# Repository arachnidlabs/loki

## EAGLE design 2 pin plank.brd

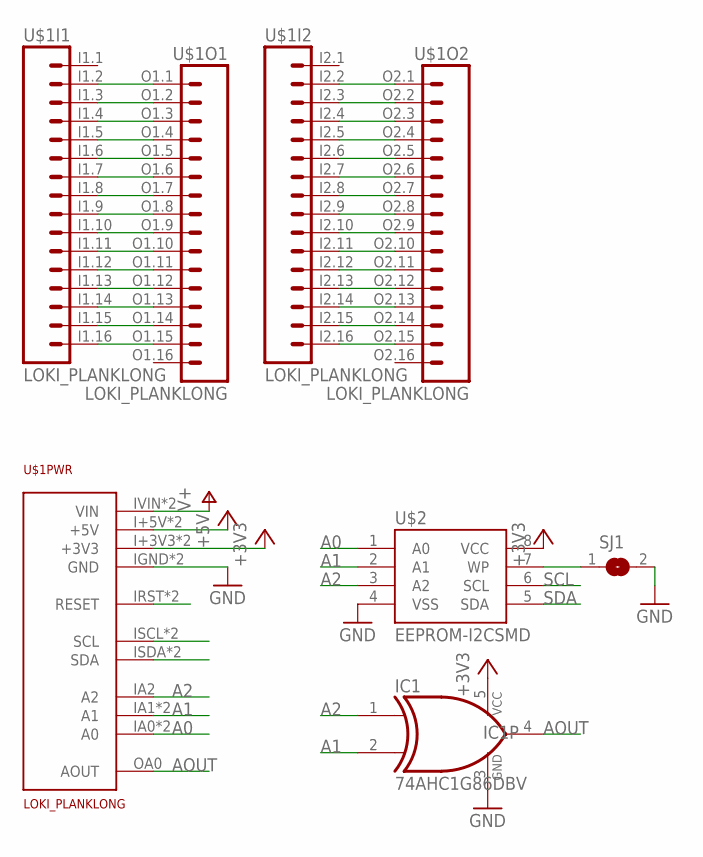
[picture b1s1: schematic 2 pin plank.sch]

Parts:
IC1: 74AHC1G86DBV; SOT23-5
SJ1: SJ
U$1: LOKI_PLANKLONG; PLANK_LONG
U$2: EEPROM-I2CSMD; SO08

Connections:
+3V3: IC1.5 (VCC), U$1.I+3V3 (+3V3), U$1.O+3V3 (+3V3), U$2.8 (VCC)
+5V: U$1.I+5V (+5V), U$1.O+5V (+5V)
A0: U$1.IA0 (A0), U$1.OA1 (A0), U$2.1 (A0)
A1: IC1.2 (I1), U$1.IA1 (A1), U$1.OA2 (A1), U$2.2 (A1)
A2: IC1.1 (I0), U$1.IA2 (A2), U$2.3 (A2)
AOUT: IC1.4 (O), U$1.OA0 (AOUT)
GND: IC1.3 (GND), SJ1.2, U$1.IGND (GND), U$1.OGND (GND), U$2.4 (VSS)
unnamed: U$1.I1.16 (16), U$1.O1.15 (15)
unnamed: U$1.I1.15 (15), U$1.O1.14 (14)
unnamed: U$1.I1.14 (14), U$1.O1.13 (13)
unnamed: U$1.I1.13 (13), U$1.O1.12 (12)
unnamed: U$1.I1.12 (12), U$1.O1.11 (11)
unnamed: U$1.I1.11 (11), U$1.O1.10 (10)
unnamed: U$1.I1.10 (10), U$1.O1.9 (9)
unnamed: U$1.I1.9 (9), U$1.O1.8 (8)
unnamed: U$1.I1.8 (8), U$1.O1.7 (7)
unnamed: U$1.I1.7 (7), U$1.O1.6 (6)
unnamed: U$1.I1.6 (6), U$1.O1.5 (5)
unnamed: U$1.I1.5 (5), U$1.O1.4 (4)
unnamed: U$1.I1.4 (4), U$1.O1.3 (3)
unnamed: U$1.I1.3 (3), U$1.O1.2 (2)
unnamed: U$1.I1.2 (2), U$1.O1.1 (1)
unnamed: U$1.I2.16 (16), U$1.O2.15 (15)
unnamed: U$1.I2.15 (15), U$1.O2.14 (14)
unnamed: U$1.I2.14 (14), U$1.O2.13 (13)
unnamed: U$1.I2.13 (13), U$1.O2.12 (12)
unnamed: U$1.I2.12 (12), U$1.O2.11 (11)
unnamed: U$1.I2.11 (11), U$1.O2.10 (10)
unnamed: U$1.I2.10 (10), U$1.O2.9 (9)
unnamed: U$1.I2.9 (9), U$1.O2.8 (8)
unnamed: U$1.I2.8 (8), U$1.O2.7 (7)
unnamed: U$1.I2.7 (7), U$1.O2.6 (6)
unnamed: U$1.I2.6 (6), U$1.O2.5 (5)
unnamed: U$1.I2.5 (5), U$1.O2.4 (4)
unnamed: U$1.I2.4 (4), U$1.O2.3 (3)
unnamed: U$1.I2.3 (3), U$1.O2.2 (2)
unnamed: U$1.I2.2 (2), U$1.O2.1 (1)
unnamed: SJ1.1, U$2.7 (WP)
unnamed: U$1.IRST (RESET), U$1.ORST (RESET)
SCL: U$1.ISCL (SCL), U$1.OSCL (SCL), U$2.6 (SCL)
SDA: U$1.ISDA (SDA), U$1.OSDA (SDA), U$2.5 (SDA)
V+: U$1.IVIN (VIN), U$1.OVIN (VIN)

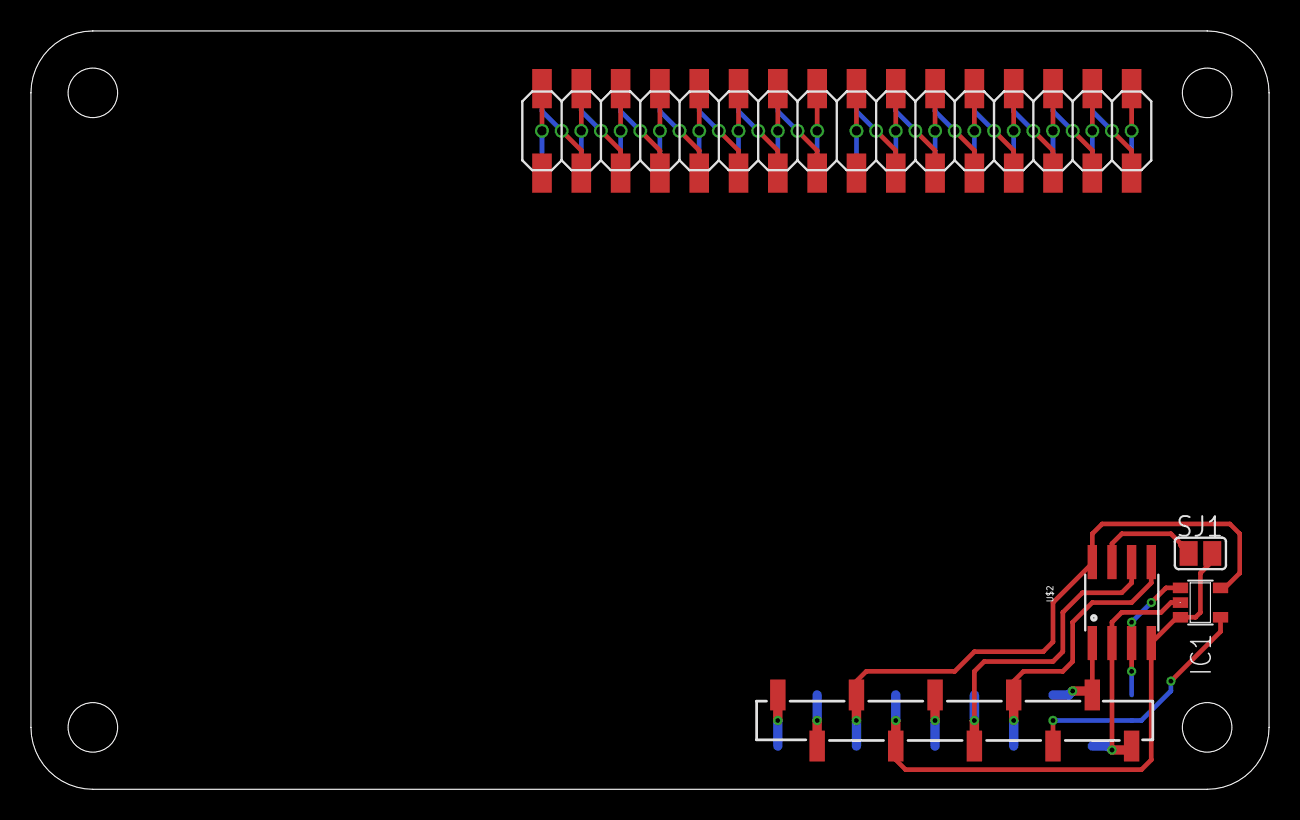
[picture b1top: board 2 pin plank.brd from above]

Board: 2 copper layers, 80.0 x 49.0 mm, 4 parts (0 on the bottom side), 42 nets.

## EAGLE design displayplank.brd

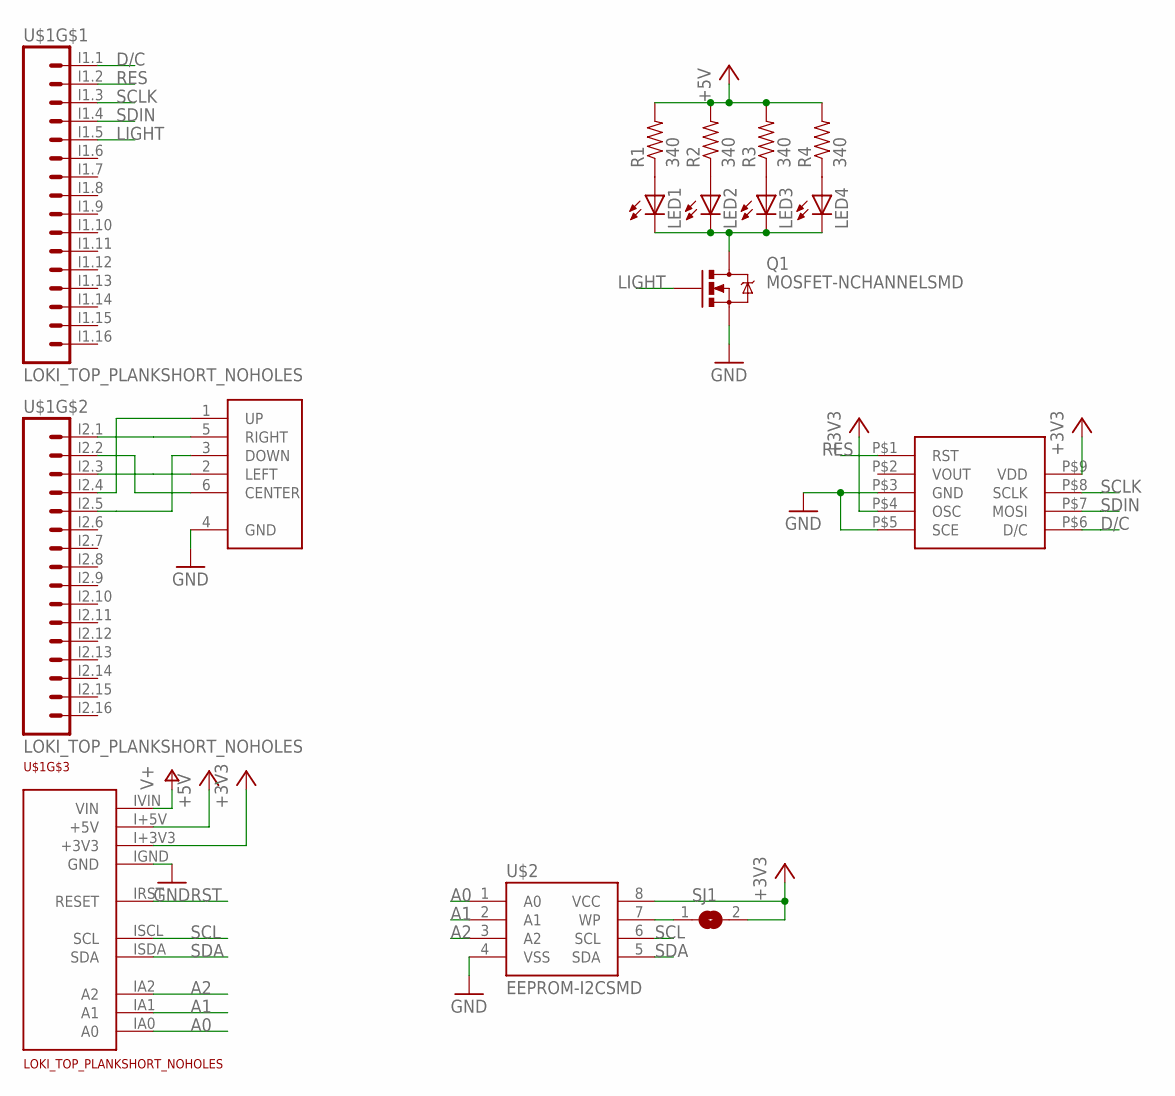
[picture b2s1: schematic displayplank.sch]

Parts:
LED1, LED2, LED3, LED4: LEDSML0805; SML0805
Q1: MOSFET-NCHANNELSMD; SOT23-3
R1, R2, R3, R4: 340; 0603-RES
SJ1: SJ
U$1: LOKI_TOP_PLANKSHORT_NOHOLES; TOP_PLANK_SHORT_NOHOLES
U$2: EEPROM-I2CSMD; SO08
U$3: JOYSTICK-10MM
U$5: 5110-SCREEN

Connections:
+3V3: SJ1.2, U$1.I+3V3 (+3V3), U$2.8 (VCC), U$5.P$4 (OSC), U$5.P$9 (VDD)
+5V: R1.2, R2.2, R3.2, R4.2, U$1.I+5V (+5V)
A0: U$1.IA0 (A0), U$2.1 (A0)
A1: U$1.IA1 (A1), U$2.2 (A1)
A2: U$1.IA2 (A2), U$2.3 (A2)
D/C: U$1.I1.1 (1), U$5.P$6 (D/C)
GND: Q1.2 (S), U$1.IGND (GND), U$2.4 (VSS), U$3.4 (GND), U$5.P$3 (GND), U$5.P$5 (SCE)
LIGHT: Q1.1 (G), U$1.I1.5 (5)
unnamed: SJ1.1, U$2.7 (WP)
unnamed: LED1.A, R1.1
unnamed: LED2.A, R2.1
unnamed: LED3.A, R3.1
unnamed: LED4.A, R4.1
unnamed: LED1.C, LED2.C, LED3.C, LED4.C, Q1.3 (D)
unnamed: U$1.I2.4 (4), U$3.1 (UP)
unnamed: U$1.I2.2 (2), U$3.6 (CENTER)
unnamed: U$1.I2.3 (3), U$3.2 (LEFT)
unnamed: U$1.I2.5 (5), U$3.3 (DOWN)
unnamed: U$1.I2.1 (1), U$3.5 (RIGHT)
RES: U$1.I1.2 (2), U$5.P$1 (RST)
RST: U$1.IRST (RESET)
SCL: U$1.ISCL (SCL), U$2.6 (SCL)
SCLK: U$1.I1.3 (3), U$5.P$8 (SCLK)
SDA: U$1.ISDA (SDA), U$2.5 (SDA)
SDIN: U$1.I1.4 (4), U$5.P$7 (MOSI)
V+: U$1.IVIN (VIN)

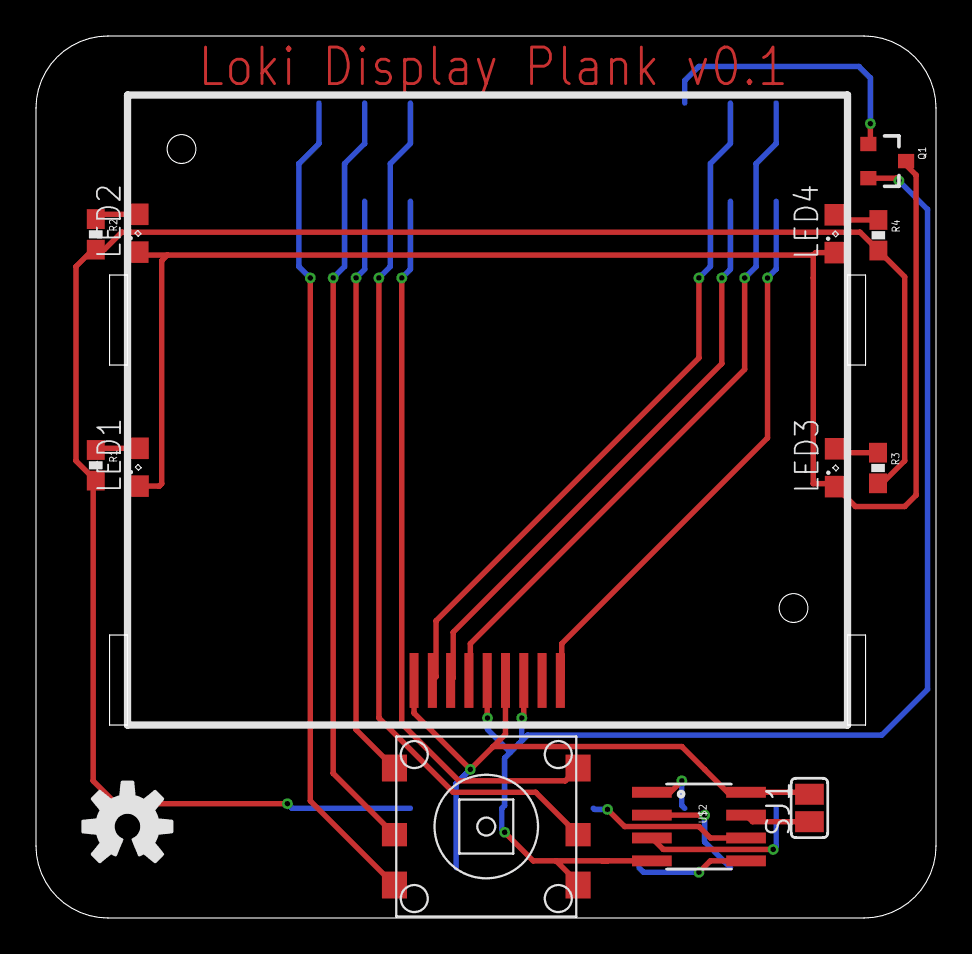
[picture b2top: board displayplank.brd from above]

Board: 2 copper layers, 50.0 x 49.0 mm, 15 parts (0 on the bottom side), 24 nets.

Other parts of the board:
U$4: OSHW-LOGO-M

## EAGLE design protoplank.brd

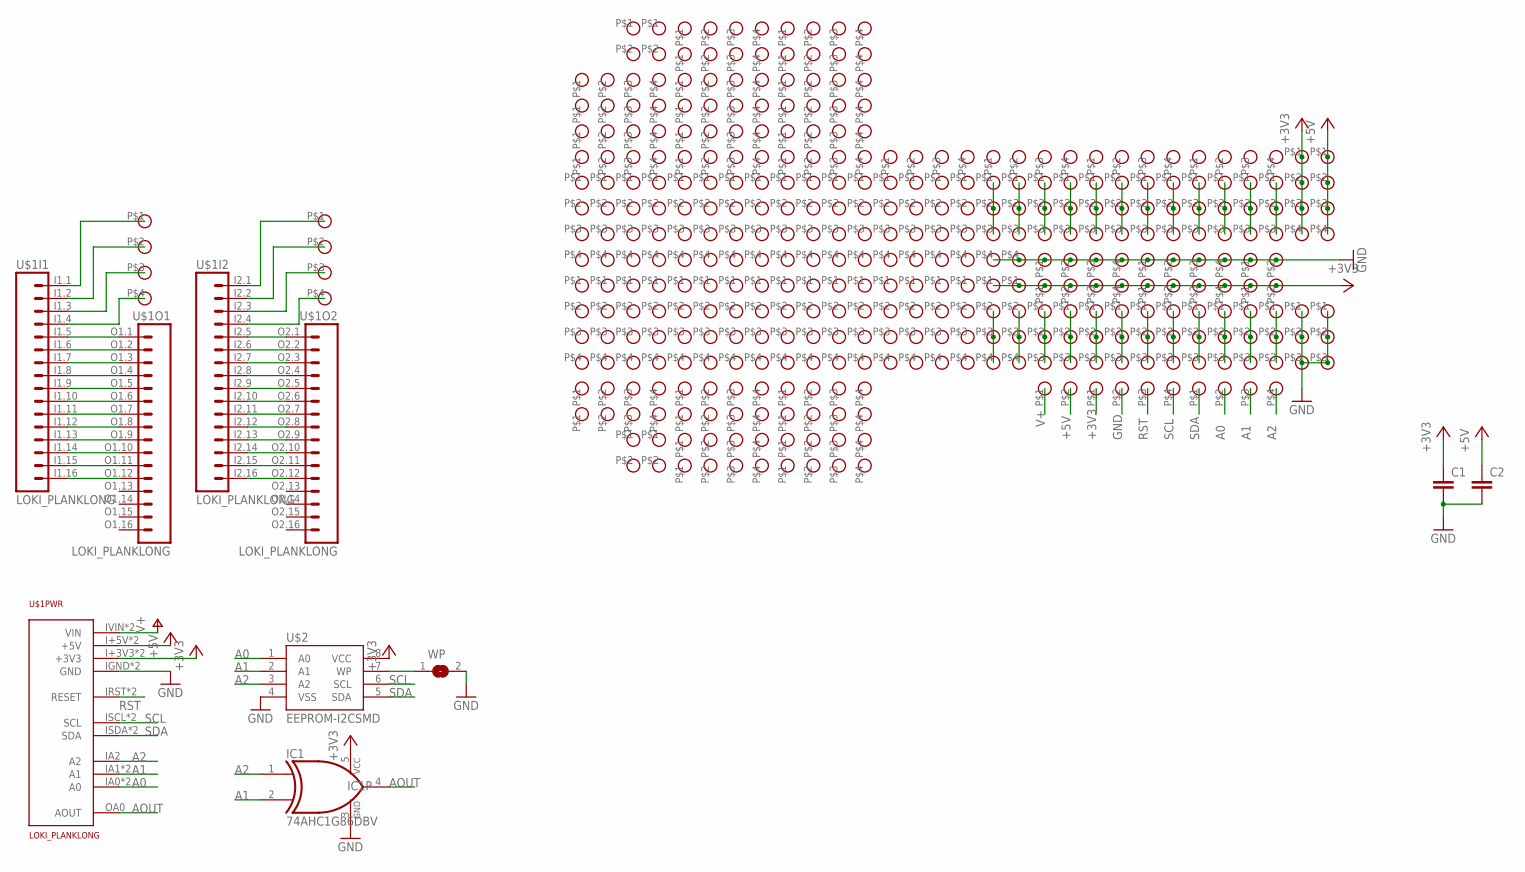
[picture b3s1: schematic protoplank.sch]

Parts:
C1, C2: CAPPTH; CAP-PTH-SMALL
IC1: 74AHC1G86DBV; SOT23-5
U$1: LOKI_PLANKLONG; PLANK_LONG
U$2: EEPROM-I2CSMD; SO08
U$3, U$4, U$5, U$6, U$7, U$8, U$9, U$10, U$11, U$12, U$13, U$14, U$15, U$16, U$17, U$18, U$19, U$20, U$21, U$22, U$78, U$80: PROTOPAD-3
U$23, U$24, U$25, U$26, U$34, U$35, U$36, U$37, U$38, U$39, U$40, U$41, U$42, U$43, U$44, U$45, U$46, U$47, U$48, U$49, U$50, U$51, U$52, U$53, U$54, U$55, U$56, U$57, U$58, U$59, U$60, U$61, U$62, U$63, U$64, U$65, U$66, U$67, U$68, U$69, U$70, U$71, U$72, U$73, U$74, U$75, U$76, U$77, U$79, U$81, U$82, U$83, U$84, U$85, U$86, U$87, U$88, U$89, U$90, U$91, U$92, U$93, U$94, U$95, U$96, U$97, U$98, U$99, U$100, U$101, U$102, U$103: PROTOPAD-4SQUARE; PROTOPAD-4
U$27, U$28, U$104, U$105, U$106, U$107: PROTOPAD-2SQUARE; PROTOPAD-2
U$29, U$30, U$31, U$32: PROTOPAD-4ROUND; PROTOPAD-4-ROUND
U$33: PROTOPAD-2ROUND; PROTOPAD-2-ROUND
WP: SJ

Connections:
+3V3: C1.1, IC1.5 (VCC), U$1.I+3V3 (+3V3), U$1.O+3V3 (+3V3), U$2.8 (VCC), U$25.P$1, U$25.P$2, U$25.P$3, U$25.P$4, U$26.P$1, U$26.P$2, U$26.P$3, U$26.P$4, U$28.P$1, U$28.P$2, U$32.P$1, U$35.P$1, U$36.P$1, U$77.P$1, U$77.P$2, U$77.P$3, U$77.P$4
+5V: C2.1, U$1.I+5V (+5V), U$1.O+5V (+5V), U$33.P$2, U$79.P$1, U$79.P$2, U$79.P$3, U$79.P$4
A0: U$1.IA0 (A0), U$1.OA1 (A0), U$2.1 (A0), U$31.P$2
A1: IC1.2 (I1), U$1.IA1 (A1), U$1.OA2 (A1), U$2.2 (A1), U$31.P$3
A2: IC1.1 (I0), U$1.IA2 (A2), U$2.3 (A2), U$31.P$4
AOUT: IC1.4 (O), U$1.OA0 (AOUT)
GND: C1.2, C2.2, IC1.3 (GND), U$1.IGND (GND), U$1.OGND (GND), U$2.4 (VSS), U$23.P$1, U$23.P$2, U$23.P$3, U$23.P$4, U$24.P$1, U$24.P$2, U$24.P$3, U$24.P$4, U$27.P$1, U$27.P$2, U$32.P$2, U$34.P$4, U$37.P$4, U$78.P$1, U$78.P$2, U$78.P$3, U$80.P$1, U$80.P$2, U$80.P$3, WP.2
unnamed: U$1.I1.16 (16), U$1.O1.12 (12)
unnamed: U$1.I1.15 (15), U$1.O1.11 (11)
unnamed: U$1.I1.14 (14), U$1.O1.10 (10)
unnamed: U$1.I1.13 (13), U$1.O1.9 (9)
unnamed: U$1.I1.12 (12), U$1.O1.8 (8)
unnamed: U$1.I1.11 (11), U$1.O1.7 (7)
unnamed: U$1.I1.10 (10), U$1.O1.6 (6)
unnamed: U$1.I1.9 (9), U$1.O1.5 (5)
unnamed: U$1.I1.8 (8), U$1.O1.4 (4)
unnamed: U$1.I1.7 (7), U$1.O1.3 (3)
unnamed: U$1.I1.6 (6), U$1.O1.2 (2)
unnamed: U$1.I1.5 (5), U$1.O1.1 (1)
unnamed: U$1.I2.16 (16), U$1.O2.12 (12)
unnamed: U$1.I2.15 (15), U$1.O2.11 (11)
unnamed: U$1.I2.14 (14), U$1.O2.10 (10)
unnamed: U$1.I2.13 (13), U$1.O2.9 (9)
unnamed: U$1.I2.12 (12), U$1.O2.8 (8)
unnamed: U$1.I2.11 (11), U$1.O2.7 (7)
unnamed: U$1.I2.10 (10), U$1.O2.6 (6)
unnamed: U$1.I2.9 (9), U$1.O2.5 (5)
unnamed: U$1.I2.8 (8), U$1.O2.4 (4)
unnamed: U$1.I2.7 (7), U$1.O2.3 (3)
unnamed: U$1.I2.6 (6), U$1.O2.2 (2)
unnamed: U$1.I2.5 (5), U$1.O2.1 (1)
unnamed: U$1.I1.4 (4), U$29.P$4
unnamed: U$1.I1.3 (3), U$29.P$3
unnamed: U$1.I1.2 (2), U$29.P$2
unnamed: U$1.I1.1 (1), U$29.P$1
unnamed: U$1.I2.4 (4), U$30.P$4
unnamed: U$1.I2.3 (3), U$30.P$3
unnamed: U$2.7 (WP), WP.1
unnamed: U$3.P$1, U$3.P$2, U$3.P$3
unnamed: U$1.I2.2 (2), U$30.P$2
unnamed: U$1.I2.1 (1), U$30.P$1
unnamed: U$4.P$1, U$4.P$2, U$4.P$3
unnamed: U$5.P$1, U$5.P$2, U$5.P$3
unnamed: U$6.P$1, U$6.P$2, U$6.P$3
unnamed: U$7.P$1, U$7.P$2, U$7.P$3
unnamed: U$8.P$1, U$8.P$2, U$8.P$3
unnamed: U$9.P$1, U$9.P$2, U$9.P$3
unnamed: U$10.P$1, U$10.P$2, U$10.P$3
unnamed: U$11.P$1, U$11.P$2, U$11.P$3
unnamed: U$12.P$1, U$12.P$2, U$12.P$3
unnamed: U$13.P$1, U$13.P$2, U$13.P$3
unnamed: U$14.P$1, U$14.P$2, U$14.P$3
unnamed: U$15.P$1, U$15.P$2, U$15.P$3
unnamed: U$16.P$1, U$16.P$2, U$16.P$3
unnamed: U$17.P$1, U$17.P$2, U$17.P$3
unnamed: U$18.P$1, U$18.P$2, U$18.P$3
unnamed: U$19.P$1, U$19.P$2, U$19.P$3
unnamed: U$20.P$1, U$20.P$2, U$20.P$3
unnamed: U$21.P$1, U$21.P$2, U$21.P$3
unnamed: U$22.P$1, U$22.P$2, U$22.P$3
unnamed: U$34.P$1, U$34.P$2, U$34.P$3
unnamed: U$37.P$1, U$37.P$2, U$37.P$3
unnamed: U$35.P$2, U$35.P$3, U$35.P$4
unnamed: U$36.P$2, U$36.P$3, U$36.P$4
RST: U$1.IRST (RESET), U$1.ORST (RESET), U$32.P$3
SCL: U$1.ISCL (SCL), U$1.OSCL (SCL), U$2.6 (SCL), U$32.P$4
SDA: U$1.ISDA (SDA), U$1.OSDA (SDA), U$2.5 (SDA), U$31.P$1
V+: U$1.IVIN (VIN), U$1.OVIN (VIN), U$33.P$1

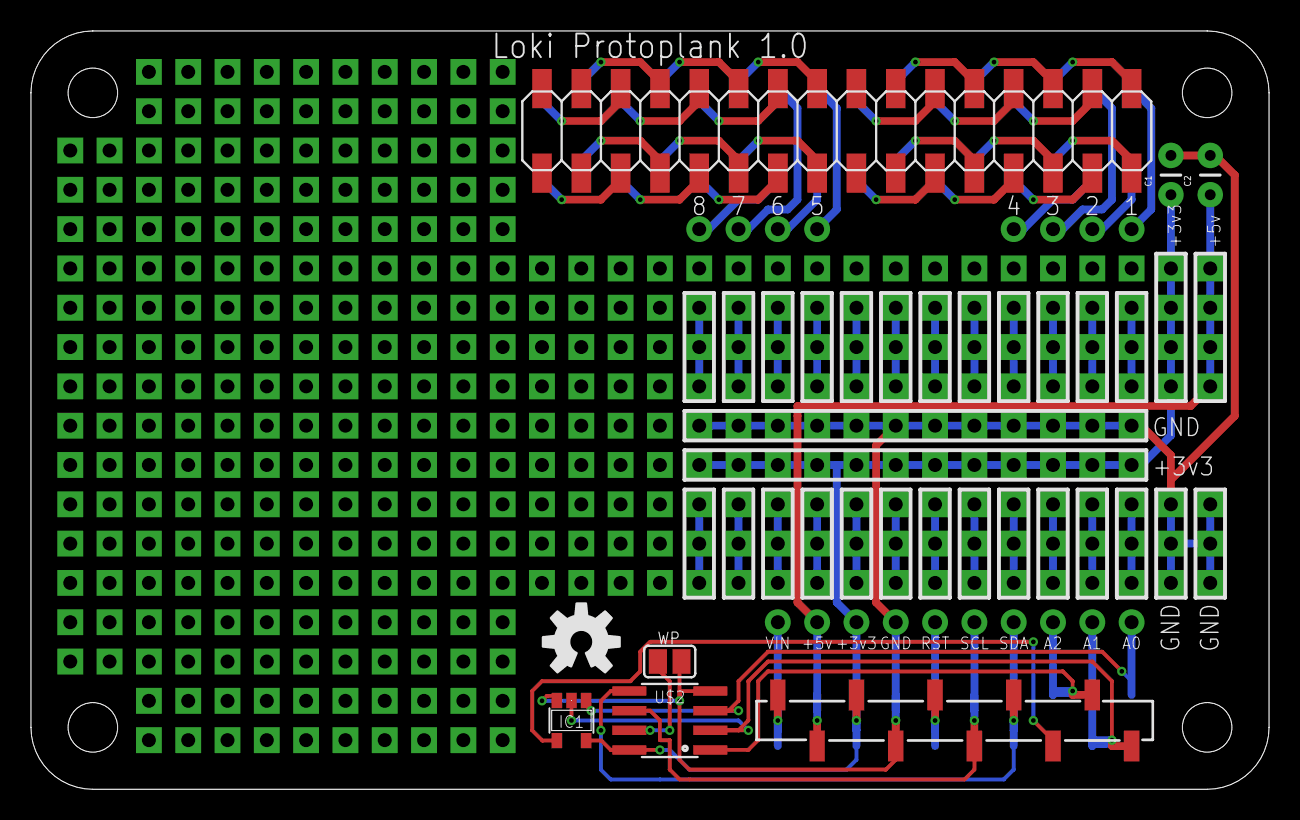
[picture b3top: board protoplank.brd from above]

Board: 2 copper layers, 80.0 x 49.0 mm, 112 parts (0 on the bottom side), 68 nets.

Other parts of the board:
U$108: OSHW-LOGO-M

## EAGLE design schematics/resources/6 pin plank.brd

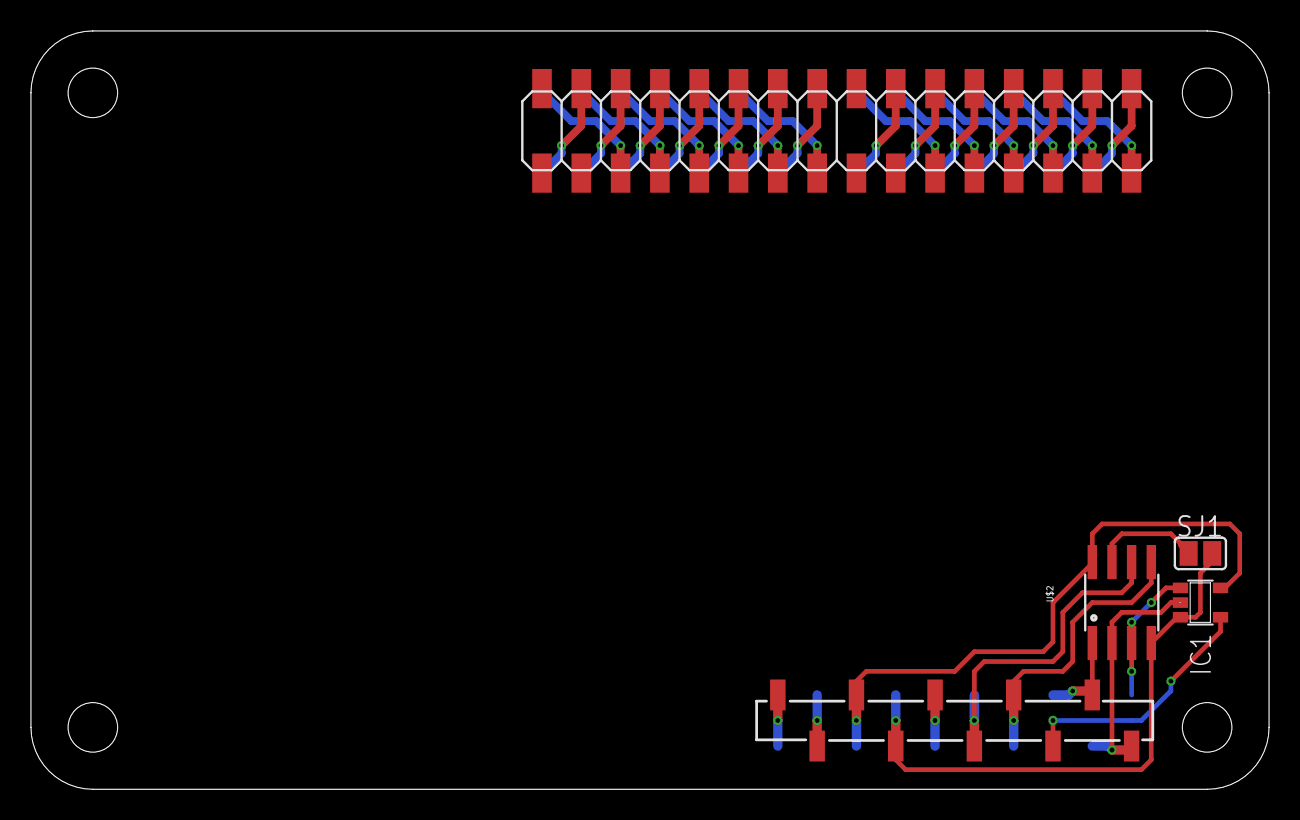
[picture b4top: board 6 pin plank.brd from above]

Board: 2 copper layers, 80.0 x 49.0 mm, 4 parts (0 on the bottom side), 38 nets.

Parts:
IC1: 74AHC1G86DBV; SOT23-5
SJ1: SJ
U$1: LOKI_PLANKLONG; PLANK_LONG
U$2: EEPROM-I2CSMD; SO08

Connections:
+3V3: IC1.5, U$1.I+3V3, U$1.O+3V3, U$2.8
+5V: U$1.I+5V, U$1.O+5V
A0: U$1.IA0, U$1.OA1, U$2.1
A1: IC1.2, U$1.IA1, U$1.OA2, U$2.2
A2: IC1.1, U$1.IA2, U$2.3
AOUT: IC1.4, U$1.OA0
GND: IC1.3, SJ1.2, U$1.IGND, U$1.OGND, U$2.4
unnamed: U$1.I1.16, U$1.O1.13
unnamed: U$1.I1.15, U$1.O1.12
unnamed: U$1.I1.14, U$1.O1.11
unnamed: U$1.I1.13, U$1.O1.10
unnamed: U$1.I1.12, U$1.O1.9
unnamed: U$1.I1.11, U$1.O1.8
unnamed: U$1.I1.10, U$1.O1.7
unnamed: U$1.I1.9, U$1.O1.6
unnamed: U$1.I1.8, U$1.O1.5
unnamed: U$1.I1.7, U$1.O1.4
unnamed: U$1.I1.6, U$1.O1.3
unnamed: U$1.I1.5, U$1.O1.2
unnamed: U$1.I1.4, U$1.O1.1
unnamed: U$1.I2.16, U$1.O2.13
unnamed: U$1.I2.15, U$1.O2.12
unnamed: U$1.I2.14, U$1.O2.11
unnamed: U$1.I2.13, U$1.O2.10
unnamed: U$1.I2.12, U$1.O2.9
unnamed: U$1.I2.11, U$1.O2.8
unnamed: U$1.I2.10, U$1.O2.7
unnamed: U$1.I2.9, U$1.O2.6
unnamed: U$1.I2.8, U$1.O2.5
unnamed: U$1.I2.7, U$1.O2.4
unnamed: U$1.I2.6, U$1.O2.3
unnamed: U$1.I2.5, U$1.O2.2
unnamed: U$1.I2.4, U$1.O2.1
unnamed: SJ1.1, U$2.7
unnamed: U$1.IRST, U$1.ORST
SCL: U$1.ISCL, U$1.OSCL, U$2.6
SDA: U$1.ISDA, U$1.OSDA, U$2.5
V+: U$1.IVIN, U$1.OVIN

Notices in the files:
parts and their libraries:
SparkFun-DigitalIC: Licensing: CC v3.0 Share-Alike You are welcome to use this library for commercial purposes.
